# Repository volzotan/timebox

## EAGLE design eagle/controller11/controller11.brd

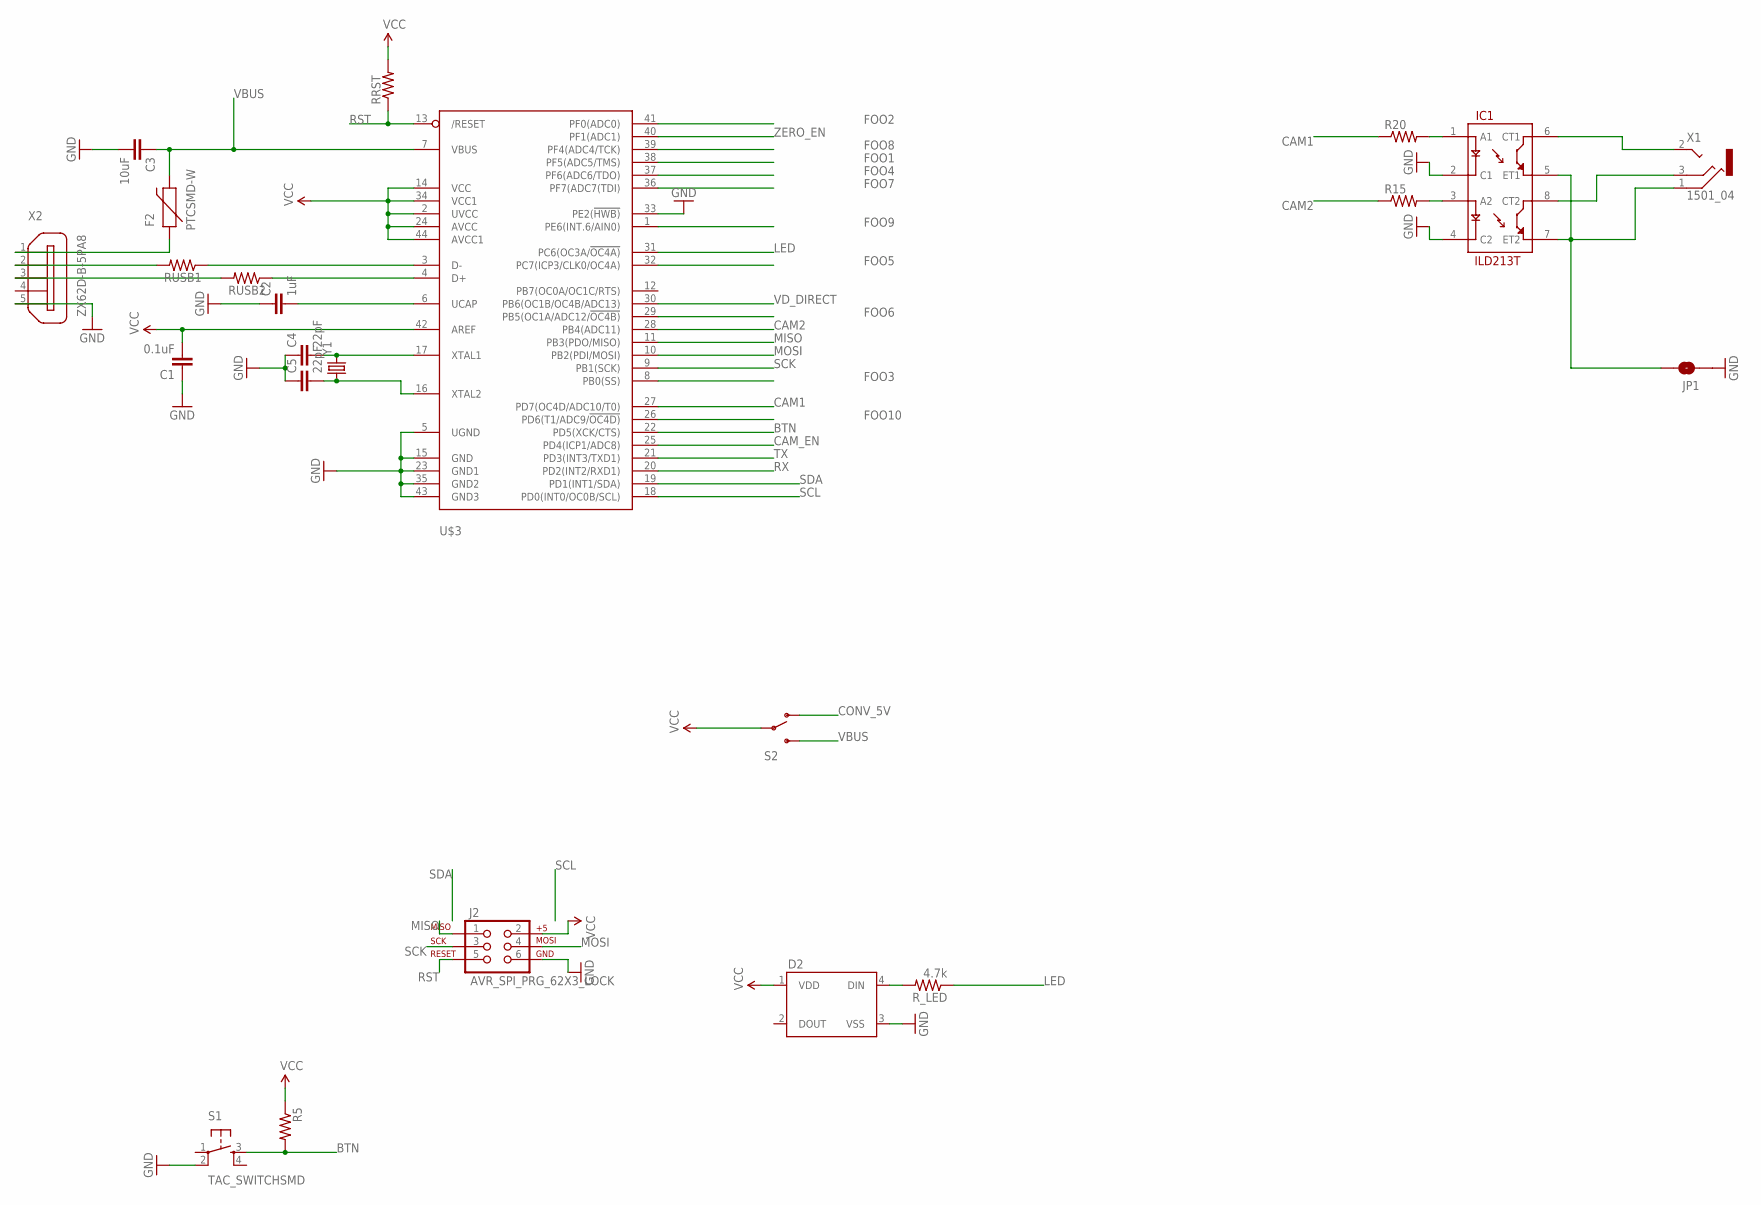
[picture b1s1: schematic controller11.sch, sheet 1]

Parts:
C1: 0.1uF; 1206
C2: 1uF; 1206
C3: 10uF; 1206
C4, C5: 22pF; 1206
D2: WS2812B
F2: PTCSMD-W; PTC-1206-WIDE
IC1: ILD213T; SO08
J2: AVR_SPI_PRG_62X3_LOCK; 2X3_LOCK
JP1: JUMPER-PAD-2-NOYES_SILK; PAD-JUMPER-2-NO_YES_SILK
R5, R15, R20: RESISTOR1206; 1206
RRST: RESISTOR1206; 1206
RUSB1, RUSB2: RESISTOR1206; 1206
R_LED: 4.7k; 1206
S1: TAC_SWITCHSMD; TACTILE-SWITCH-SMD
S2: SWITCH-SPDTSMD2; SWITCH-SPDT-SMD
U$3: ATMEGA32U4-AU; TQFP44
X1: 1501_04; 1501_05
X2: ZX62D-B-5PA8
Y1: CRYSTALCRYSTAL-SMD-5X3-16MHZ; CRYSTAL-SMD-5X3

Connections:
BTN: R5.2, S1.3, U$3.22 (PD5(XCK/CTS))
CAM1: R20.1, U$3.27 (PD7(OC4D/ADC10/T0))
CAM2: R15.1, U$3.28 (PB4(ADC11))
CAM_EN: U$3.25 (PD4(ICP1/ADC8)); also elsewhere on the board
CONV_5V: S2.1 (O); also elsewhere on the board
FOO1: U$3.38 (PF5(ADC5/TMS))
FOO2: U$3.41 (PF0(ADC0))
FOO3: U$3.8 (PB0(SS))
FOO4: U$3.37 (PF6(ADC6/TDO))
FOO5: U$3.32 (PC7(ICP3/CLK0/OC4A))
FOO6: U$3.29 (PB5(OC1A/ADC12/!OC4B))
FOO7: U$3.36 (PF7(ADC7(TDI))
FOO8: U$3.39 (PF4(ADC4/TCK))
FOO9: U$3.1 (PE6(INT.6/AIN0))
FOO10: U$3.26 (PD6(T1/ADC9/!OC4D))
GND: C1.1, C2.1, C3.2, C4.1, C5.1, D2.3 (VSS), IC1.2 (C1), IC1.4 (C2), J2.6, JP1.1, S1.2, U$3.5 (UGND), U$3.15 (GND), U$3.23 (GND1), U$3.33 (PE2(!HWB)), U$3.35 (GND2), U$3.43 (GND3), X2.5; also elsewhere on the board
LED: R_LED.1, U$3.31 (PC6(OC3A/!OC4A))
MISO: J2.1, U$3.11 (PB3(PDO/MISO))
MOSI: J2.4, U$3.10 (PB2(PDI/MOSI))
unnamed: RUSB1.1, U$3.3 (D-)
unnamed: RUSB2.1, U$3.4 (D+)
unnamed: D2.4 (DIN), R_LED.2
unnamed: C4.2, U$3.17 (XTAL1), Y1.3 (2)
unnamed: C5.2, U$3.16 (XTAL2), Y1.1
unnamed: RUSB1.2, X2.2
unnamed: RUSB2.2, X2.3
unnamed: IC1.6 (CT1), X1.2
unnamed: IC1.8 (CT2), X1.3
unnamed: IC1.3 (A2), R15.2
unnamed: IC1.1 (A1), R20.2
unnamed: C2.2, U$3.6 (UCAP)
unnamed: IC1.5 (ET1), IC1.7 (ET2), JP1.2, X1.1
unnamed: F2.1, X2.1
RST: J2.5, RRST.1, U$3.13 (/RESET)
RX: U$3.20 (PD2(INT2/RXD1)); also elsewhere on the board
SCK: J2.3, U$3.9 (PB1(SCK))
SCL: U$3.18 (PD0(INT0/OC0B/SCL))
SDA: U$3.19 (PD1(INT1/SDA))
TX: U$3.21 (PD3(INT3/TXD1)); also elsewhere on the board
VBUS: C3.1, F2.2, S2.3 (S), U$3.7 (VBUS)
VCC: C1.2, D2.1 (VDD), J2.2, R5.1, RRST.2, S2.2, U$3.2 (UVCC), U$3.14 (VCC), U$3.24 (AVCC), U$3.34 (VCC1), U$3.42 (AREF), U$3.44 (AVCC1); also elsewhere on the board
VD_DIRECT: U$3.30 (PB6(OC1B/OC4B/ADC13)); also elsewhere on the board
ZERO_EN: U$3.40 (PF1(ADC1)); also elsewhere on the board

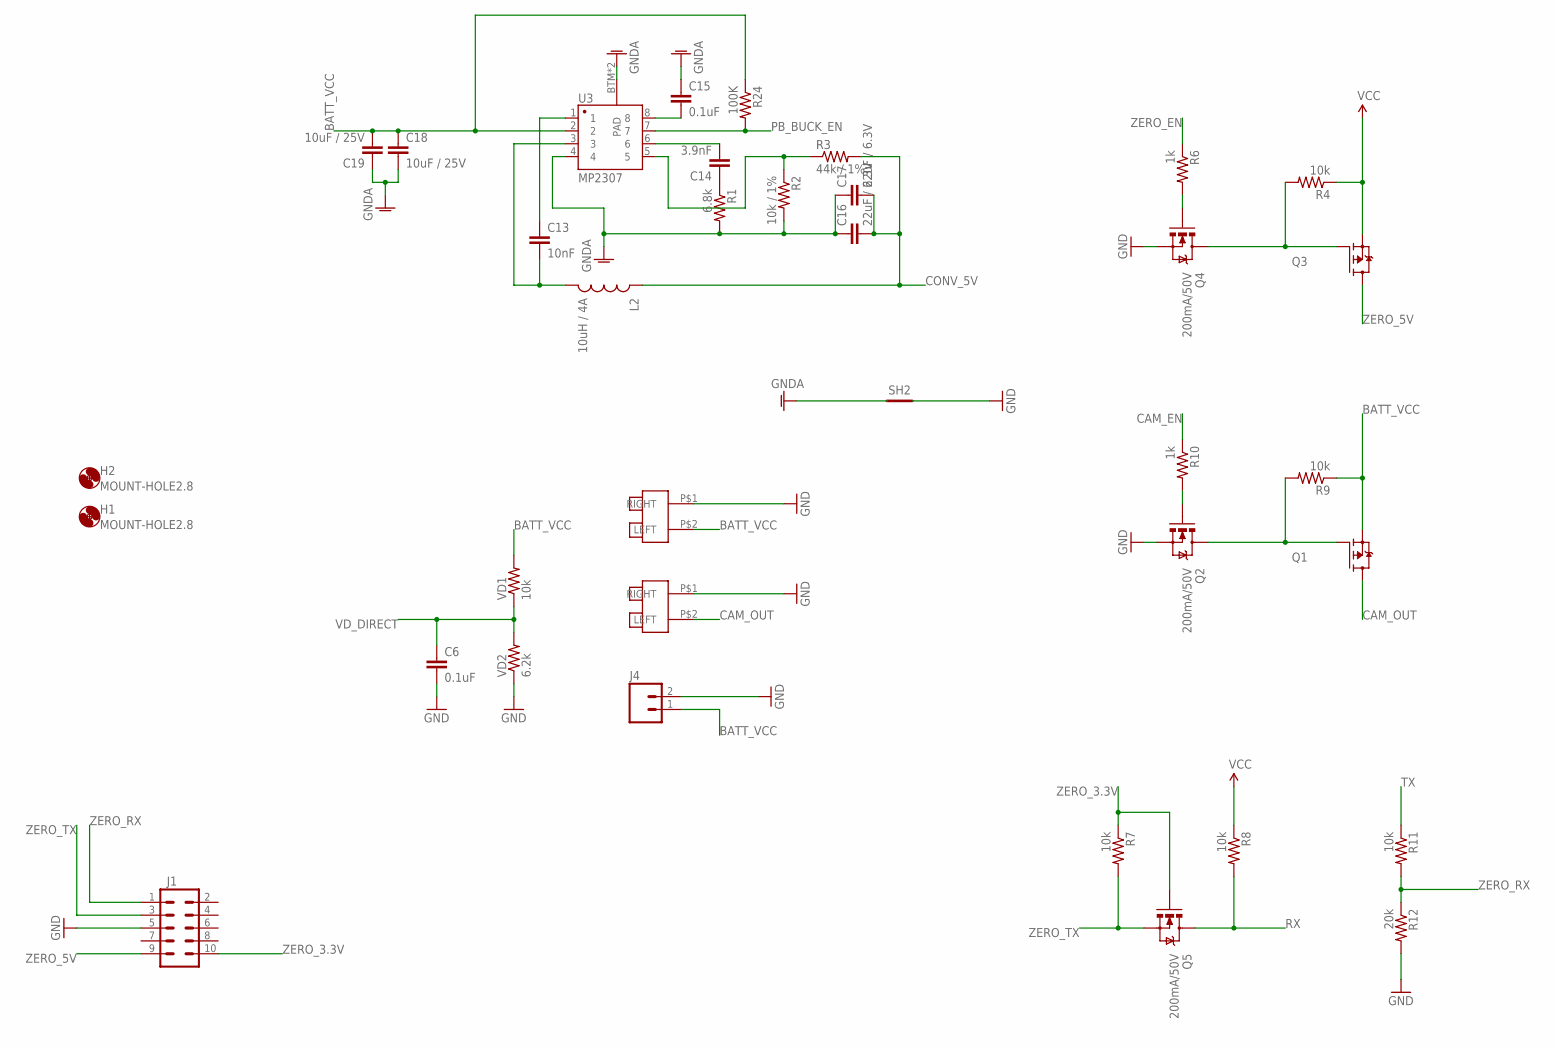
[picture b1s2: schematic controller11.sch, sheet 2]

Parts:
C6, C15: 0.1uF; 1206
C13: 10nF; 1206
C14: 3.9nF; 1206
C16, C17: 22uF / 6.3V; 1210
C18, C19: 10uF / 25V; 1210
H1, H2: MOUNT-HOLE2.8; 2,8
J1: M05X2PTH; AVR_ICSP
J4: M02LOCK; 1X02_LOCK
L2: 10uH / 4A; SRU1038
Q1, Q3: FDD4141TO252; TO252
Q2, Q4, Q5: 200mA/50V; SOT23-3
R1: 6.8k; 1206
R2: 10k / 1%; 1206
R3: 44k / 1%; 1206
R4, R7, R8, R9, R11: 10k; 1206
R6, R10: 1k; 1206
R12: 20k; 1206
R24: 100K; 1206
SH2: SHORT-HT5; SHORT_TOP-50
U3: MP2307; SO08
U$4, U$5: NANOFIT2
VD1: 10k; 1206
VD2: 6.2k; 1206

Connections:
BATT_VCC: C18.1, C19.2, J4.1, Q1.2 (S), R9.1, R24.1, U3.2, U$4.P$2 (LEFT), VD1.2
CAM_EN: R10.1; also elsewhere on the board
CAM_OUT: Q1.3 (D), U$5.P$2 (LEFT)
CONV_5V: C16.2, C17.2, L2.1, R3.2; also elsewhere on the board
GND: C6.2, J1.5, J4.2, Q2.2 (S), Q4.2 (S), R12.2, SH2.2, U$4.P$1 (RIGHT), U$5.P$1 (RIGHT), VD2.1; also elsewhere on the board
GNDA: C15.1, C16.1, C17.1, C18.2, C19.1, R1.2, R2.2, SH2.1, U3.4, U3.BTM (PAD), U3.P$1 (PAD)
unnamed: Q1.1 (G), Q2.3 (D), R9.2
unnamed: Q4.1 (G), R6.2
unnamed: Q3.1 (G), Q4.3 (D), R4.2
unnamed: Q2.1 (G), R10.2
unnamed: C15.2, U3.8
unnamed: C13.2, L2.2, U3.3
unnamed: C13.1, U3.1
unnamed: C14.1, R1.1
unnamed: C14.2, U3.6
unnamed: R2.1, R3.1, U3.5
PB_BUCK_EN: R24.2, U3.7
RX: Q5.3 (D), R8.2; also elsewhere on the board
TX: R11.1; also elsewhere on the board
VCC: Q3.2 (S), R4.1, R8.1; also elsewhere on the board
VD_DIRECT: C6.1, VD1.1, VD2.2; also elsewhere on the board
ZERO_3.3V: J1.10, Q5.1 (G), R7.1
ZERO_5V: J1.9, Q3.3 (D)
ZERO_EN: R6.1; also elsewhere on the board
ZERO_RX: J1.1, R11.2, R12.1
ZERO_TX: J1.3, Q5.2 (S), R7.2

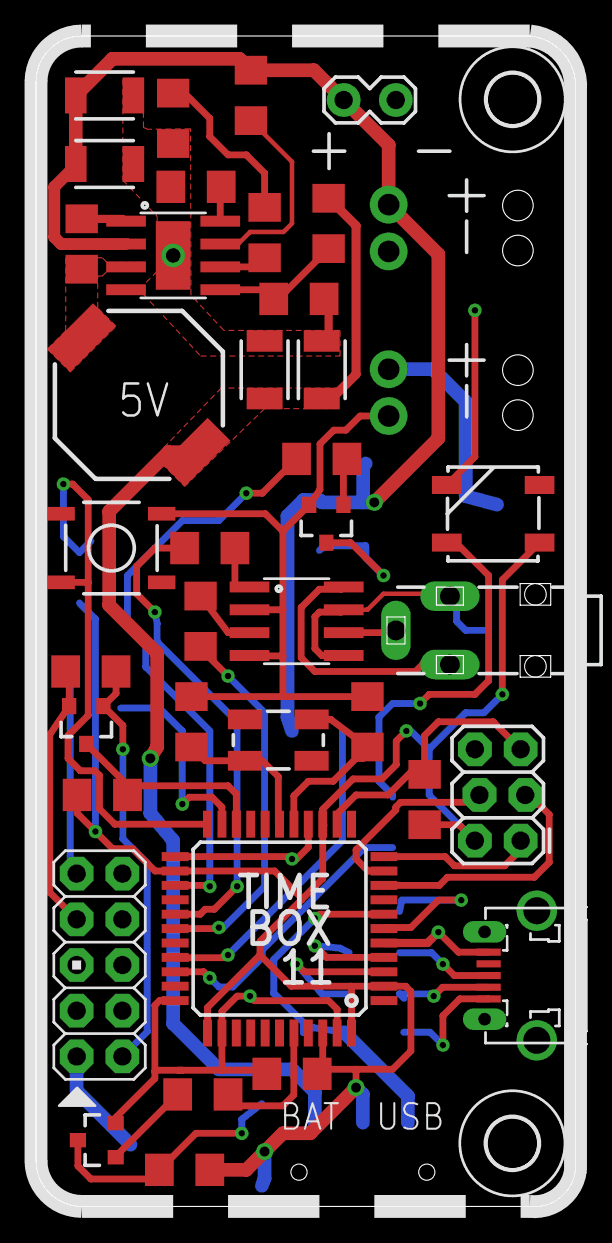
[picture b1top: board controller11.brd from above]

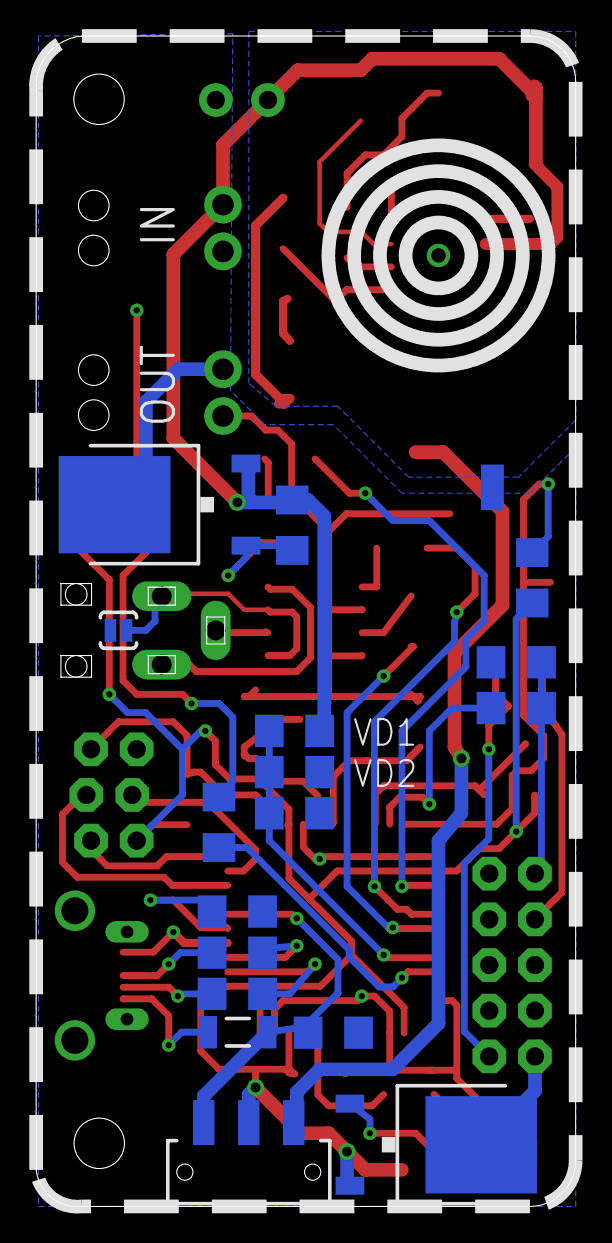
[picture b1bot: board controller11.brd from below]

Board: 2 copper layers, 30.0 x 65.0 mm, 59 parts (18 on the bottom side), 49 nets.

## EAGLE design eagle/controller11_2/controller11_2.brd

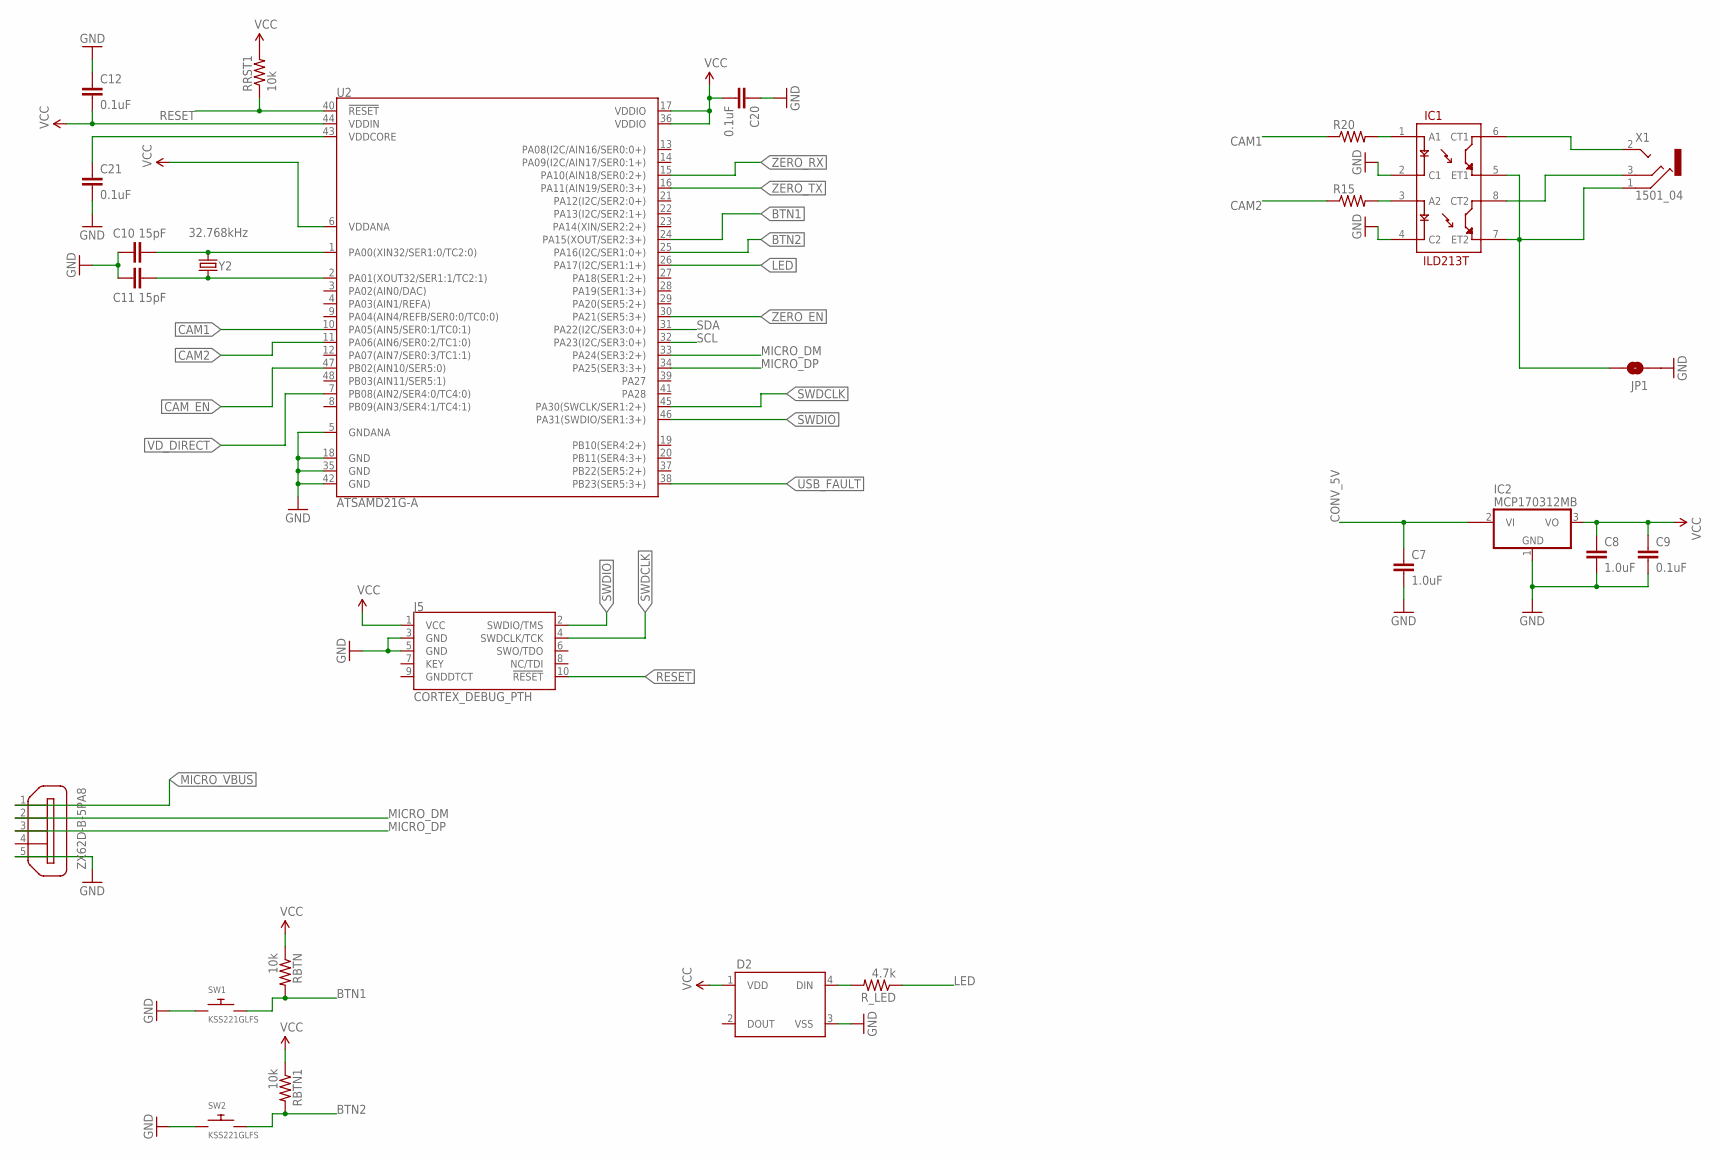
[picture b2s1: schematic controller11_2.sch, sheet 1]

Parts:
C7: 1.0uF; 0805
C8: 1.0uF; 1206
C9, C12, C20, C21: 0.1uF; 0805
C10, C11: 15pF; 0805
D2: WS2812B
IC1: ILD213T; SO08
IC2: MCP170312MB; SOT89
J5: CORTEX_DEBUG_PTH; 2X5-PTH-1.27MM
JP1: JUMPER-PAD-2-NOYES_SILK; PAD-JUMPER-2-NO_YES_SILK
R15, R20: RESISTOR0805-RES; 0805
RBTN, RBTN1: 10k; 0805
RRST1: 10k; 0805
R_LED: 4.7k; 0805
SW1, SW2: KSS221GLFS; BTN_CK_KSS
U2: ATSAMD21G-A; TQFP-48
X1: 1501_04; 1501_05
X2: ZX62D-B-5PA8
Y2: 32.768kHz; CRYSTAL-SMD-3.2X1.5MM

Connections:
BTN1: RBTN.2, SW1.P$2, U2.24 (PA15(XOUT/SER2:3+))
BTN2: RBTN1.2, SW2.P$2, U2.25 (PA16(I2C/SER1:0+))
CAM1: R20.1, U2.10 (PA05(AIN5/SER0:1/TC0:1))
CAM2: R15.1, U2.11 (PA06(AIN6/SER0:2/TC1:0))
CAM_EN: U2.47 (PB02(AIN10/SER5:0)); also elsewhere on the board
CONV_5V: C7.1, IC2.2@1 (VI1); also elsewhere on the board
GND: C7.2, C8.2, C9.2, C10.1, C11.1, C12.1, C20.1, C21.2, D2.3 (VSS), IC1.2 (C1), IC1.4 (C2), IC2.1 (GND), J5.3 (GND), J5.5 (GND), JP1.1, SW1.P$1, SW2.P$1, U2.5 (GNDANA), U2.18 (GND), U2.35 (GND), U2.42 (GND), X2.5; also elsewhere on the board
LED: R_LED.1, U2.26 (PA17(I2C/SER1:1+))
MICRO_DM: U2.33 (PA24(SER3:2+)), X2.2
MICRO_DP: U2.34 (PA25(SER3:3+)), X2.3
MICRO_VBUS: X2.1
unnamed: C21.1, U2.43 (VDDCORE)
unnamed: C10.2, U2.1 (PA00(XIN32/SER1:0/TC2:0)), Y2.P$2 (2)
unnamed: D2.4 (DIN), R_LED.2
unnamed: IC1.6 (CT1), X1.2
unnamed: IC1.8 (CT2), X1.3
unnamed: IC1.3 (A2), R15.2
unnamed: IC1.1 (A1), R20.2
unnamed: C11.2, U2.2 (PA01(XOUT32/SER1:1/TC2:1)), Y2.P$1 (1)
unnamed: IC1.5 (ET1), IC1.7 (ET2), JP1.2, X1.1
RESET: J5.10 (!RESET), RRST1.1, U2.40 (!RESET!)
SCL: U2.32 (PA23(I2C/SER3:0+)); also elsewhere on the board
SDA: U2.31 (PA22(I2C/SER3:0+)); also elsewhere on the board
SWDCLK: J5.4 (SWDCLK/TCK), U2.45 (PA30(SWCLK/SER1:2+))
SWDIO: J5.2 (SWDIO/TMS), U2.46 (PA31(SWDIO/SER1:3+))
USB_FAULT: U2.38 (PB23(SER5:3+))
VCC: C8.1, C9.1, C12.2, C20.2, D2.1 (VDD), IC2.3 (VO), J5.1 (VCC), RBTN.1, RBTN1.1, RRST1.2, U2.6 (VDDANA), U2.17 (VDDIO), U2.36 (VDDIO), U2.44 (VDDIN); also elsewhere on the board
VD_DIRECT: U2.7 (PB08(AIN2/SER4:0/TC4:0)); also elsewhere on the board
ZERO_EN: U2.30 (PA21(SER5:3+)); also elsewhere on the board
ZERO_RX: U2.15 (PA10(AIN18/SER0:2+)); also elsewhere on the board
ZERO_TX: U2.16 (PA11(AIN19/SER0:3+)); also elsewhere on the board

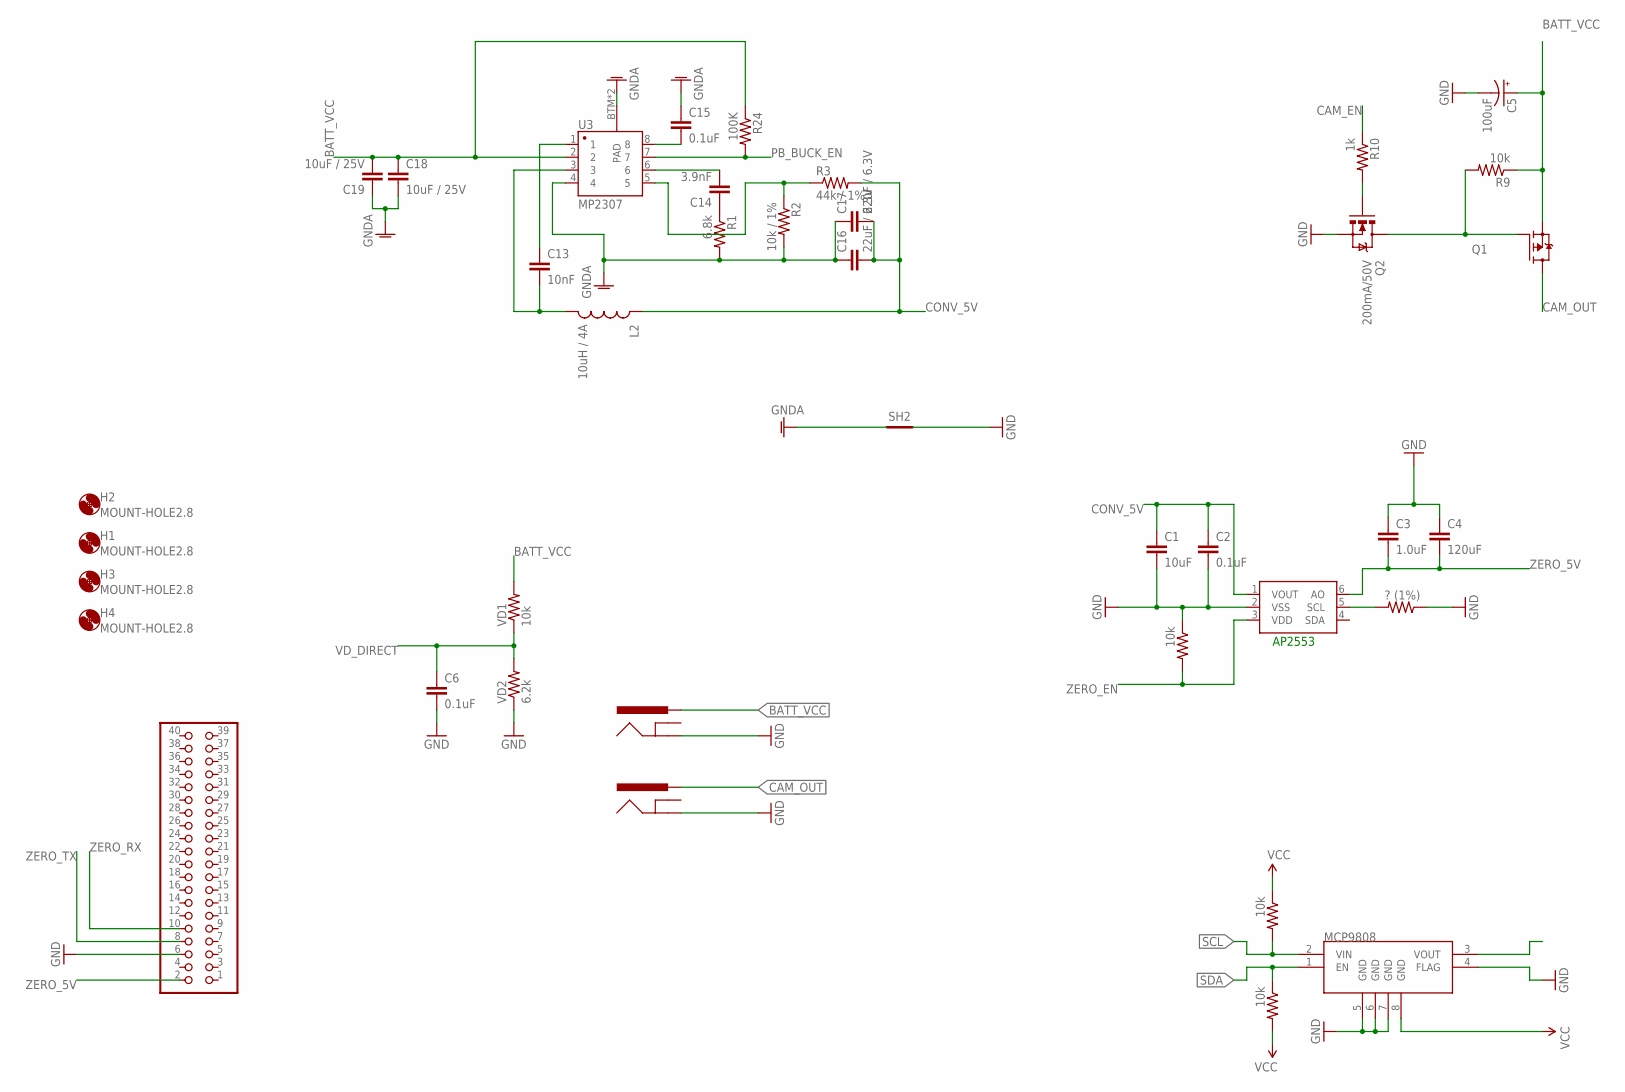
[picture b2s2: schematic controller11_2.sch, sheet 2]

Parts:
AP2553: MCP4725; SOT23-6
C1: 10uF; 0805
C2: 0.1uF; 0805
C3: 1.0uF; 0805
C4: 120uF; 1206
C5: 100uF; PANASONIC_D
C6, C15: 0.1uF; 1206
C13: 10nF; 1206
C14: 3.9nF; 1206
C16, C17: 22uF / 6.3V; 1210
C18, C19: 10uF / 25V; 1210
H1, H2, H3, H4: MOUNT-HOLE2.8; 2,8
J1, J2: POWER_JACKPTH_BREAD; POWER_JACK_PTH_BREAD
JP2: PINHD-2X20; 2X20
L2: 10uH / 4A; SRU1038
MCP9808: V_REG_MIC5216; MSOP8
Q1: FDD4141TO252; TO252
Q2: 200mA/50V; SOT23-3
R1: 6.8k; 1206
R2: 10k / 1%; 1206
R3: 44k / 1%; 1206
R9: 10k; 0805
R10: 1k; 0805
R24: 100K; 1206
R_I2C_1, R_I2C_2: 10k; 0805
R_MOSFET_USB1: ? (1%); 0805
R_MOSFET_USB3: 10k; 0805
SH2: SHORT-HT5; SHORT_TOP-50
U3: MP2307; SO08
VD1: 10k; 1206
VD2: 6.2k; 1206

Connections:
BATT_VCC: C5.+, C18.1, C19.2, J1.PWR, Q1.2 (S), R9.1, R24.1, U3.2, VD1.2
CAM_EN: R10.1; also elsewhere on the board
CAM_OUT: J2.PWR, Q1.3 (D)
CONV_5V: AP2553.1 (VOUT), C1.1, C2.1, C16.2, C17.2, L2.1, R3.2; also elsewhere on the board
GND: AP2553.2 (VSS), C1.2, C2.2, C3.1, C4.1, C5.-, C6.2, J1.GND, J2.GND, JP2.6, MCP9808.4 (FLAG), MCP9808.5 (GND), MCP9808.6 (GND), MCP9808.7 (GND), Q2.2 (S), R_MOSFET_USB1.1, R_MOSFET_USB3.1, SH2.2, VD2.1; also elsewhere on the board
GNDA: C15.1, C16.1, C17.1, C18.2, C19.1, R1.2, R2.2, SH2.1, U3.4, U3.BTM (PAD), U3.P$1 (PAD)
unnamed: Q1.1 (G), Q2.3 (D), R9.2
unnamed: AP2553.5 (SCL), R_MOSFET_USB1.2
unnamed: Q2.1 (G), R10.2
unnamed: C15.2, U3.8
unnamed: C13.2, L2.2, U3.3
unnamed: C13.1, U3.1
unnamed: C14.1, R1.1
unnamed: C14.2, U3.6
unnamed: R2.1, R3.1, U3.5
PB_BUCK_EN: R24.2, U3.7
SCL: MCP9808.2 (VIN), R_I2C_1.2; also elsewhere on the board
SDA: MCP9808.1 (EN), R_I2C_2.1; also elsewhere on the board
VCC: MCP9808.8 (GND), R_I2C_1.1, R_I2C_2.2; also elsewhere on the board
VD_DIRECT: C6.1, VD1.1, VD2.2; also elsewhere on the board
ZERO_5V: AP2553.6 (AO), C3.2, C4.2, JP2.2
ZERO_EN: AP2553.3 (VDD), R_MOSFET_USB3.2; also elsewhere on the board
ZERO_RX: JP2.10; also elsewhere on the board
ZERO_TX: JP2.8; also elsewhere on the board

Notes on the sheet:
AP2553

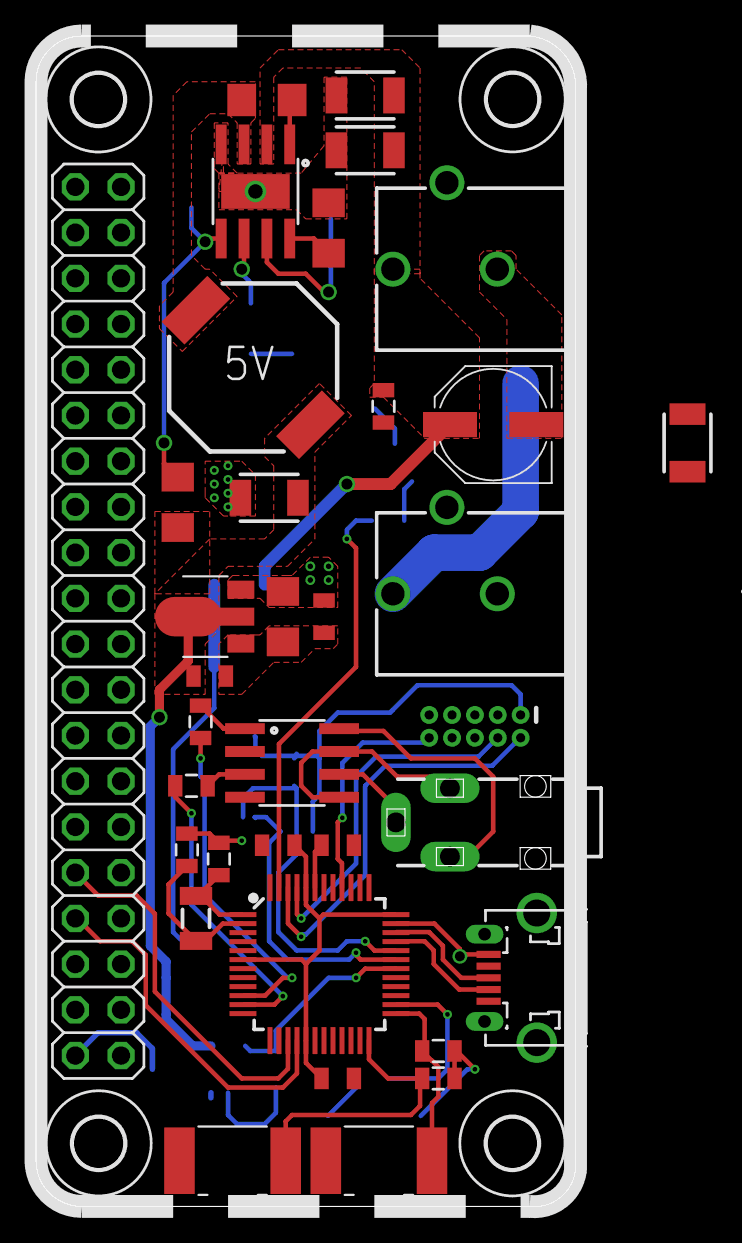
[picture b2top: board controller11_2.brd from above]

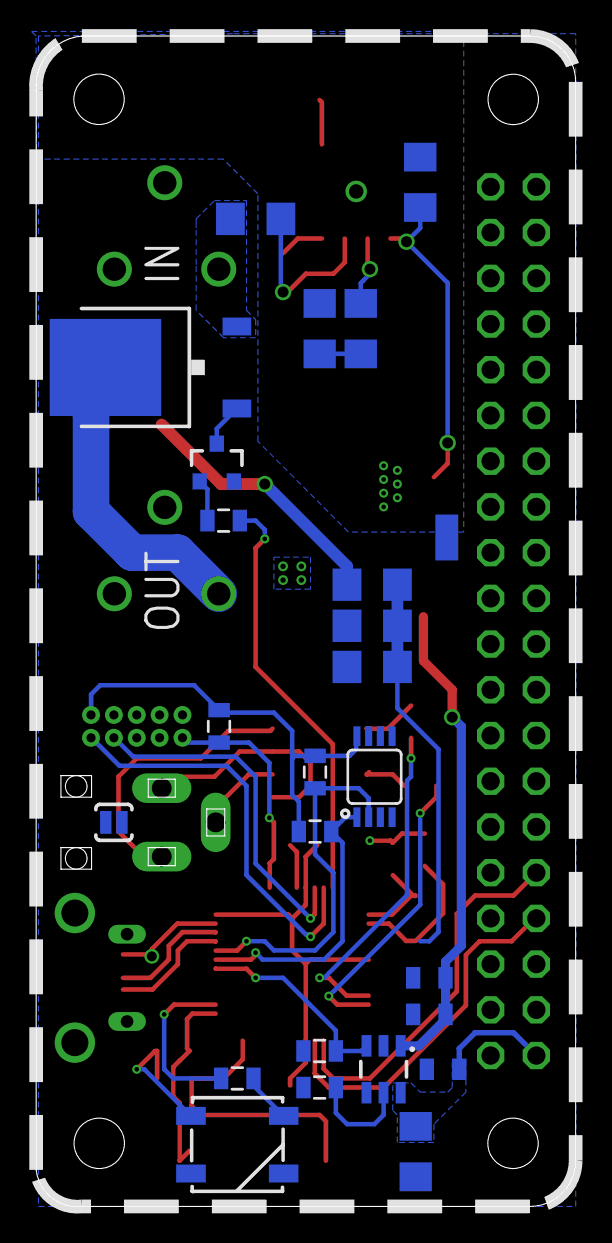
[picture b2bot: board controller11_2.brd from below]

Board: 2 copper layers, 30.0 x 65.0 mm, 64 parts (25 on the bottom side), 43 nets.

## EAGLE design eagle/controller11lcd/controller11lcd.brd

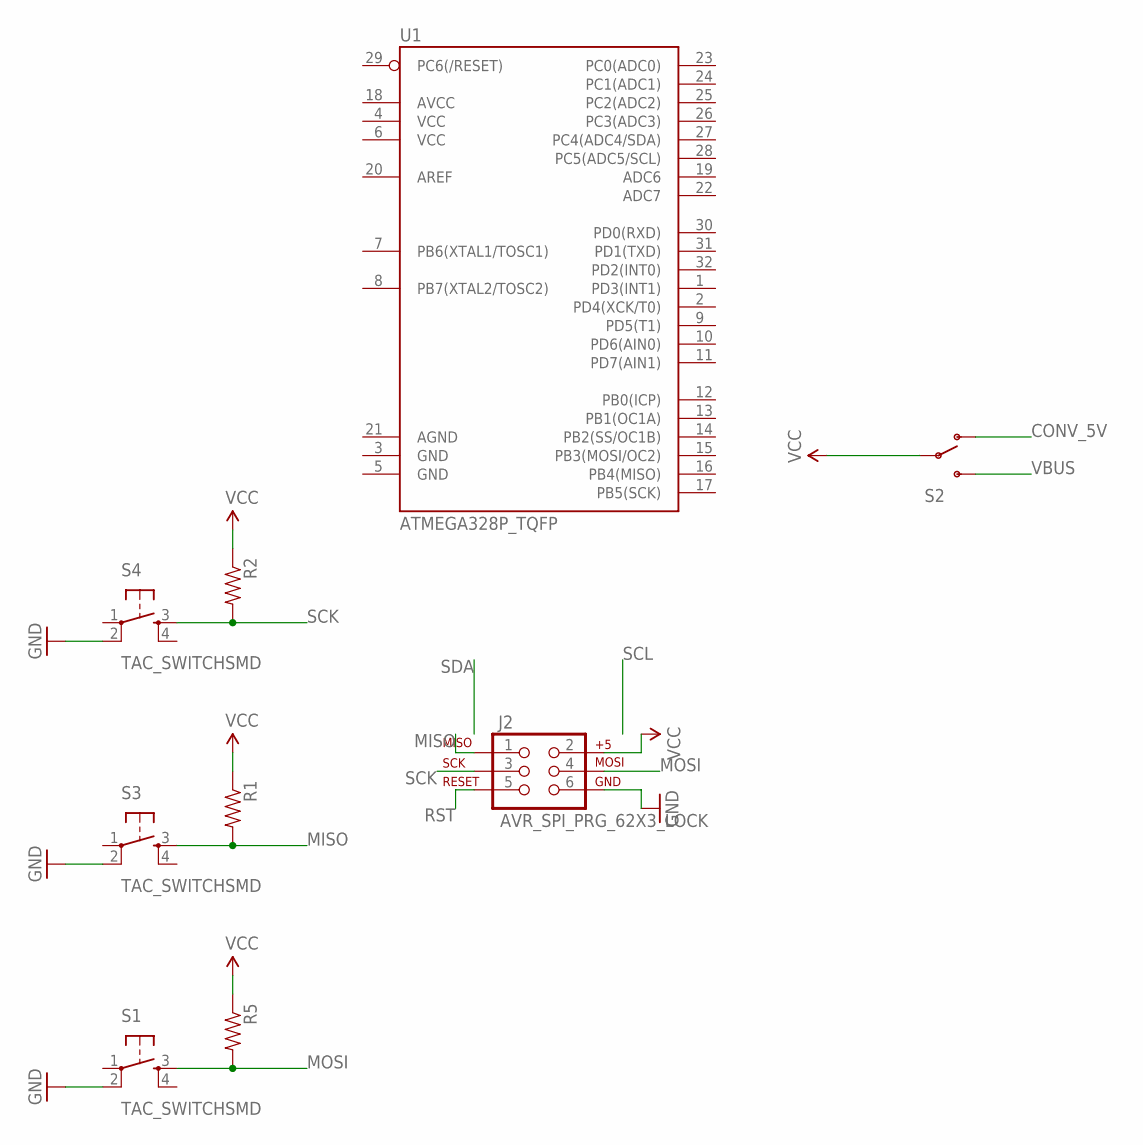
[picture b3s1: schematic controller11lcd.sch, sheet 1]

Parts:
J2: AVR_SPI_PRG_62X3_LOCK; 2X3_LOCK
R1, R2, R5: RESISTOR1206; 1206
S1, S3, S4: TAC_SWITCHSMD; TACTILE-PTH
S2: SWITCH-SPDTSMD2; SWITCH-SPDT-SMD
U1: ATMEGA328P_TQFP; TQFP32-08

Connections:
CONV_5V: S2.1 (O)
GND: J2.6, S1.2, S3.2, S4.2
MISO: J2.1, R1.2, S3.3
MOSI: J2.4, R5.2, S1.3
RST: J2.5
SCK: J2.3, R2.2, S4.3
VBUS: S2.3 (S)
VCC: J2.2, R1.1, R2.1, R5.1, S2.2

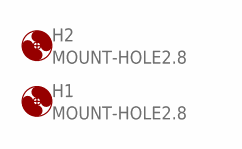
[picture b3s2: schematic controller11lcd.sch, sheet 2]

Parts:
H1, H2: MOUNT-HOLE2.8; 2,8

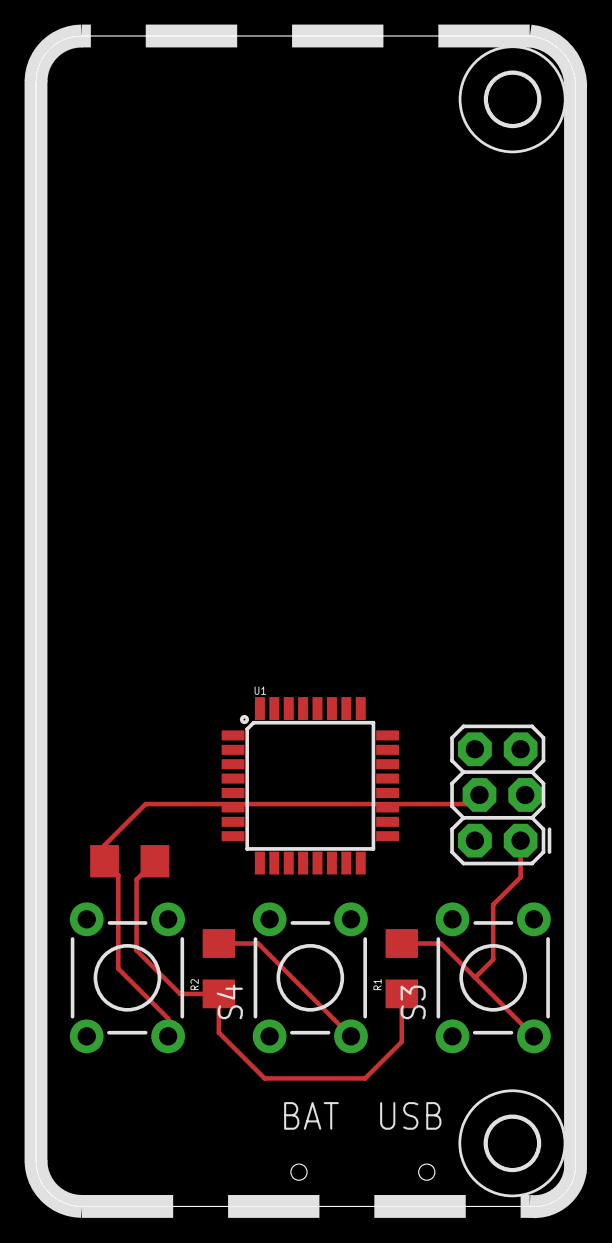
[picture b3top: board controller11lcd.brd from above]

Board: 2 copper layers, 30.0 x 65.0 mm, 11 parts (1 on the bottom side), 5 nets.

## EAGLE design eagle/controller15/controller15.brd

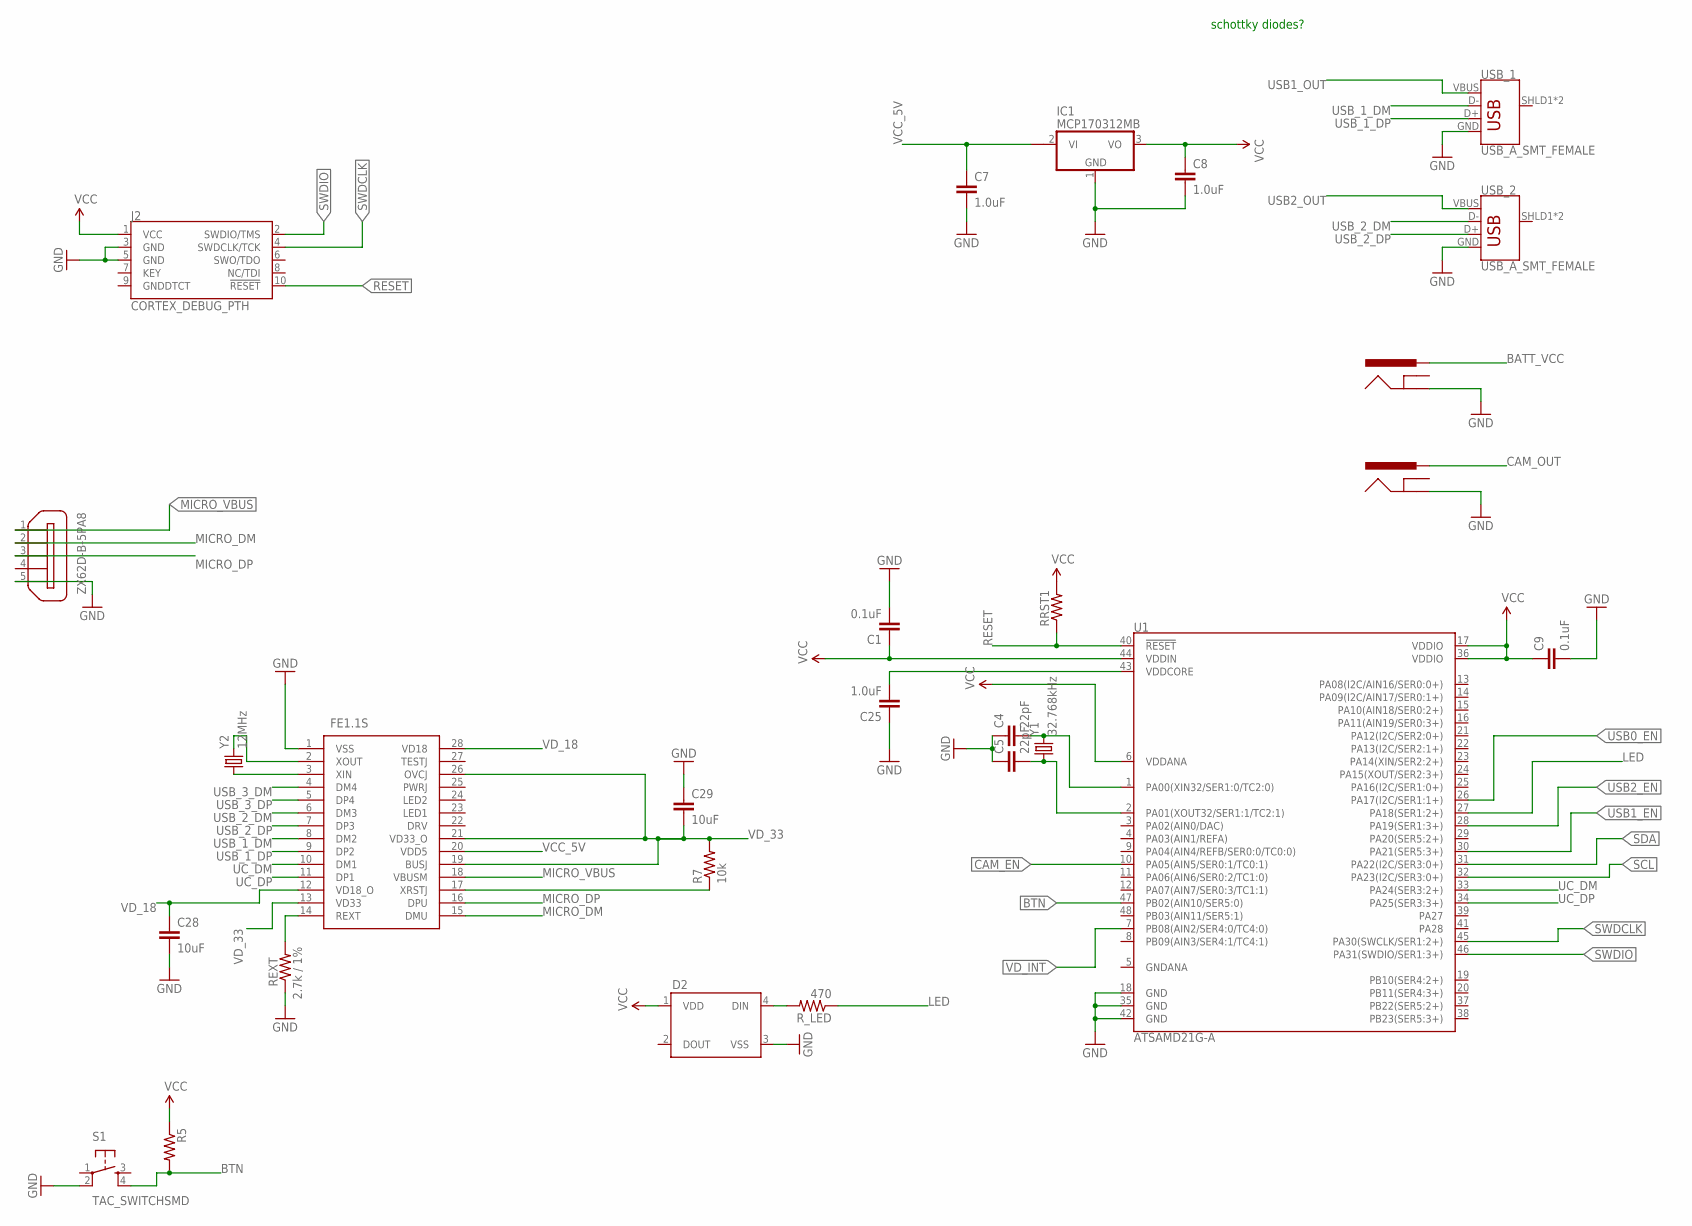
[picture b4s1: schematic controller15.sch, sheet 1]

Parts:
C1, C9: 0.1uF; 0805
C4, C5: 22pF; 0805
C7, C8: 1.0uF; 1206
C25: 1.0uF; 0805
C28, C29: 10uF; 0805
D2: WS2812B
IC1: MCP170312MB; SOT89
IC3: FE1.1S; SOP64P600X175-28N
J2: CORTEX_DEBUG_PTH; 2X5-PTH-1.27MM
J3, J4: POWER_JACKPTH_BREAD; POWER_JACK_PTH_BREAD
R5: RESISTOR0805-RES; 0805
R7: 10k; 0805
REXT: 2.7k / 1%; 0805
RRST1: RESISTOR0805-RES; 0805
R_LED: 470; 0805
S1: TAC_SWITCHSMD; TACTILE-SWITCH-SMD
U1: ATSAMD21G-A; TQFP-48
USB_1, USB_2: USB_A_SMT_FEMALE; USB-A-S-SILK-FEMALE
X2: ZX62D-B-5PA8
Y1: 32.768kHz; CRYSTAL-SMD-3.2X1.5MM
Y2: 12MHz; CRYSTAL-SMD-3.2X1.5MM

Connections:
BATT_VCC: J4.PWR; also elsewhere on the board
BTN: R5.2, S1.4, U1.47 (PB02(AIN10/SER5:0))
CAM_EN: U1.10 (PA05(AIN5/SER0:1/TC0:1)); also elsewhere on the board
CAM_OUT: J3.PWR; also elsewhere on the board
GND: C1.2, C4.1, C5.1, C7.2, C8.2, C9.2, C25.1, C28.2, C29.1, D2.3 (VSS), IC1.1 (GND), IC3.1 (VSS), J2.3 (GND), J2.5 (GND), J3.GND, J4.GND, REXT.1, S1.2, U1.18 (GND), U1.35 (GND), U1.42 (GND), USB_1.GND, USB_2.GND, X2.5; also elsewhere on the board
LED: R_LED.1, U1.27 (PA18(SER1:2+))
MICRO_DM: IC3.15 (DMU), X2.2
MICRO_DP: IC3.16 (DPU), X2.3
MICRO_VBUS: IC3.18 (VBUSM), X2.1; also elsewhere on the board
unnamed: C25.2, U1.43 (VDDCORE)
unnamed: D2.4 (DIN), R_LED.2
unnamed: C4.2, U1.1 (PA00(XIN32/SER1:0/TC2:0)), Y1.P$2 (2)
unnamed: IC3.17 (XRSTJ), R7.1
unnamed: IC3.3 (XIN), Y2.P$1 (1)
unnamed: IC3.2 (XOUT), Y2.P$2 (2)
unnamed: IC3.14 (REXT), REXT.2
unnamed: C5.2, U1.2 (PA01(XOUT32/SER1:1/TC2:1)), Y1.P$1 (1)
RESET: J2.10 (!RESET), RRST1.1, U1.40 (!RESET!)
SCL: U1.32 (PA23(I2C/SER3:0+)); also elsewhere on the board
SDA: U1.31 (PA22(I2C/SER3:0+)); also elsewhere on the board
SWDCLK: J2.4 (SWDCLK/TCK), U1.45 (PA30(SWCLK/SER1:2+))
SWDIO: J2.2 (SWDIO/TMS), U1.46 (PA31(SWDIO/SER1:3+))
UC_DM: IC3.10 (DM1), U1.33 (PA24(SER3:2+))
UC_DP: IC3.11 (DP1), U1.34 (PA25(SER3:3+))
USB0_EN: U1.26 (PA17(I2C/SER1:1+)); also elsewhere on the board
USB1_EN: U1.30 (PA21(SER5:3+)); also elsewhere on the board
USB1_OUT: USB_1.VBUS; also elsewhere on the board
USB2_EN: U1.28 (PA19(SER1:3+)); also elsewhere on the board
USB2_OUT: USB_2.VBUS; also elsewhere on the board
USB_1_DM: IC3.8 (DM2), USB_1.D-
USB_1_DP: IC3.9 (DP2), USB_1.D+
USB_2_DM: IC3.6 (DM3), USB_2.D-
USB_2_DP: IC3.7 (DP3), USB_2.D+
USB_3_DM: IC3.4 (DM4)
USB_3_DP: IC3.5 (DP4)
VCC: C1.1, C8.1, C9.1, D2.1 (VDD), IC1.3 (VO), J2.1 (VCC), R5.1, RRST1.2, U1.6 (VDDANA), U1.17 (VDDIO), U1.36 (VDDIO), U1.44 (VDDIN); also elsewhere on the board
VCC_5V: C7.1, IC1.2@1 (VI1), IC3.20 (VDD5); also elsewhere on the board
VD_18: C28.1, IC3.12 (VD18_O), IC3.28 (VD18)
VD_33: C29.2, IC3.13 (VD33), IC3.19 (BUSJ), IC3.21 (VD33_O), IC3.26 (OVCJ), R7.2
VD_INT: U1.7 (PB08(AIN2/SER4:0/TC4:0)); also elsewhere on the board

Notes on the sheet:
schottky diodes?

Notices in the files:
parts and their libraries:
SparkFun-Connectors: Licensing: Creative Commons ShareAlike 4.0 International - https://creativecommons.org/licenses/by-sa/4.0
